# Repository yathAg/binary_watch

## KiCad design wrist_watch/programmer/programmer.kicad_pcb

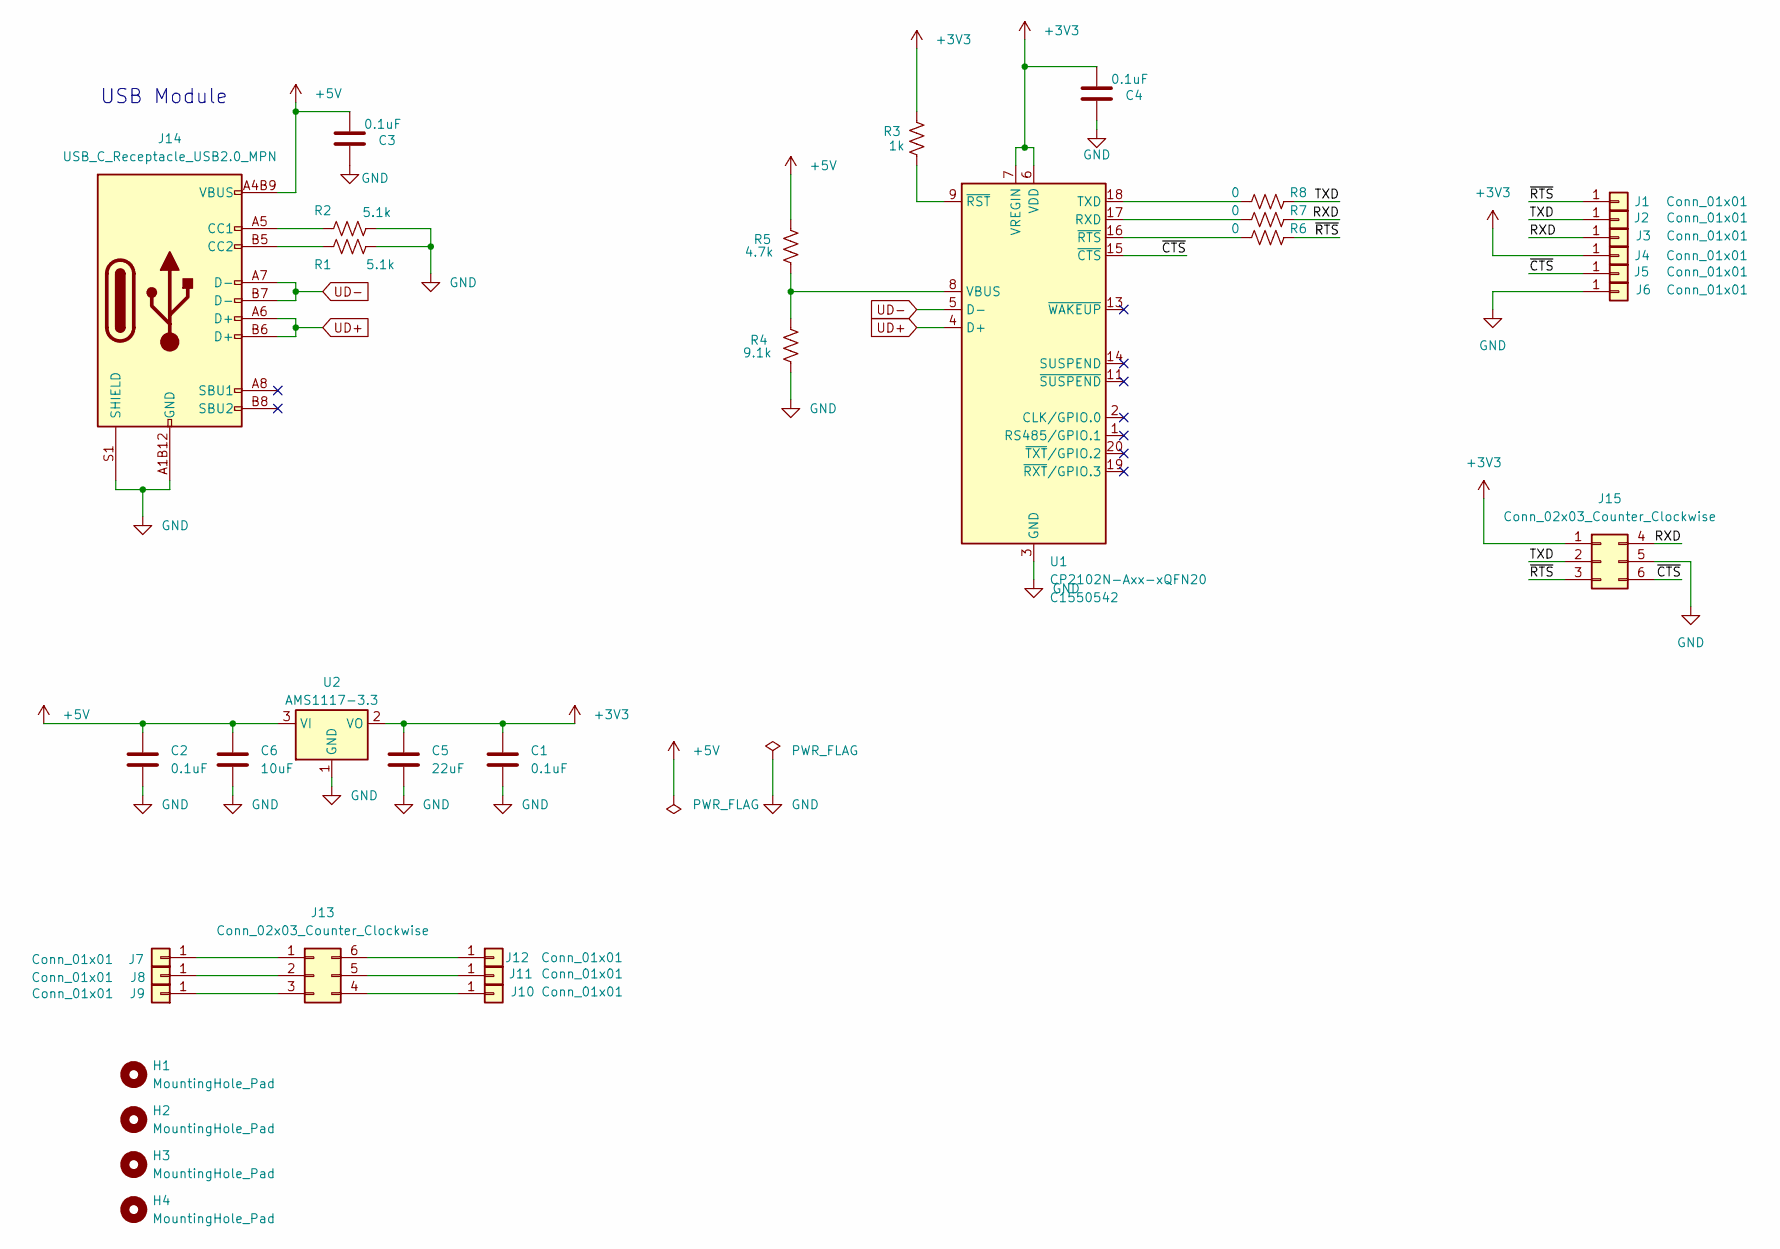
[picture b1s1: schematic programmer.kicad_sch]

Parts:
C1, C2, C3, C4: 0.1uF; C_0805_2012Metric; LCSC C1525
C5: 22uF; C_0805_2012Metric; LCSC C59461
C6: 10uF; C_0805_2012Metric; LCSC C19702
H1, H2, H3, H4: MountingHole_Pad; MountingHole_3.2mm_M3
J1, J2, J3, J4, J5, J6, J7, J8, J9, J10, J11, J12: Conn_01x01; TestPoint_Pad_D2.0mm
J13, J15: Conn_02x03_Counter_Clockwise; PinHeader_2x03_P2.54mm_Vertical
J14: USB_C_Receptacle_USB2.0_MPN; USB-C-YTC-TC16S-23; LCSC C393939
R1, R2: 5.1k; R_0805_2012Metric; LCSC C25905
R3: 1k; R_0805_2012Metric; LCSC C11702
R4: 9.1k; R_0805_2012Metric
R5: 4.7k; R_0805_2012Metric; LCSC C105871
R6, R7, R8: 0; R_0805_2012Metric
U1: CP2102N-Axx-xQFN20; SiliconLabs_QFN-20-1EP_3x3mm_P0.5mm_EP1.8x1.8mm; LCSC C1550542
U2: AMS1117-3.3; SOT-223-3_TabPin2; LCSC C94058

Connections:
+3V3: C1.1, C4.1, C5.1, J4.1, J15.1, R3.1, U1.6 (VDD), U1.7 (VREGIN), U2.2 (VO)
+5V: C2.1, C3.1, C6.1, J14.A4B9 (VBUS), J14.A9B4 (VBUS), R5.1, U2.3 (VI)
/RXD: J3.1, J15.4, R7.2
/TXD: J2.1, J15.2, R8.2
/~CTS: J5.1, J15.6, U1.15 (~CTS)
/~RTS: J1.1, J15.3, R6.2
GND: C1.2, C2.2, C3.2, C4.2, C5.2, C6.2, J6.1, J14.A1B12 (GND), J14.A12B1 (GND), J14.S1 (SHIELD), J15.5, R1.1, R2.1, R4.2, U1.3 (GND), U1.12 (GND), U1.21 (GND), U2.1 (GND)
unnamed: J10.1, J13.4
unnamed: J11.1, J13.5
unnamed: J12.1, J13.6
unnamed: J7.1, J13.1
unnamed: J8.1, J13.2
unnamed: J9.1, J13.3
unnamed: J14.A5 (CC1), R2.2
unnamed: J14.B5 (CC2), R1.2
unnamed: R7.1, U1.17 (RXD)
unnamed: R8.1, U1.18 (TXD)
unnamed: R4.1, R5.2, U1.8 (VBUS)
unnamed: R3.2, U1.9 (~RST)
unnamed: R6.1, U1.16 (~RTS)
UD+: J14.A6 (D+), J14.B6 (D+), U1.4 (D+)
UD-: J14.A7 (D-), J14.B7 (D-), U1.5 (D-)

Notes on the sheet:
USB Module

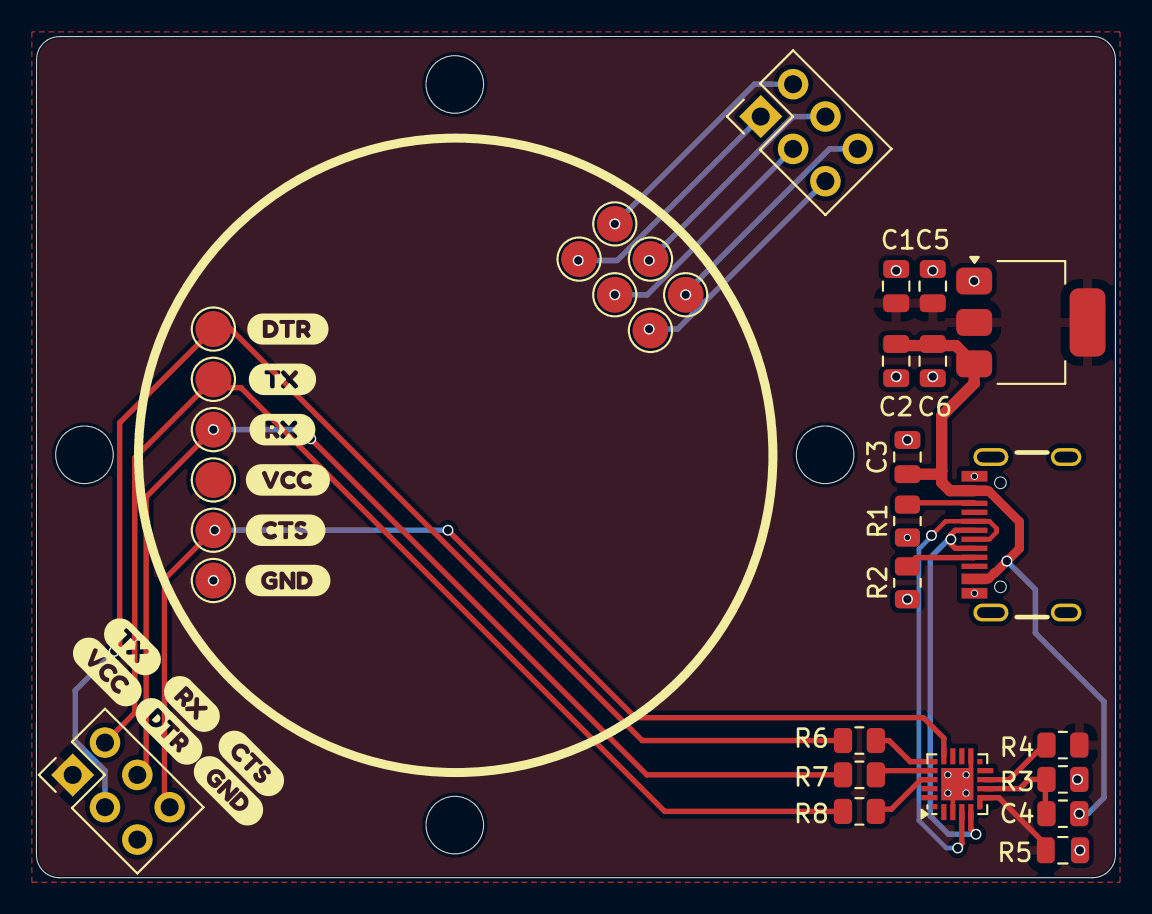
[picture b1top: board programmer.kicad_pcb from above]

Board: 2 copper layers, 59.9 x 46.7 mm, 47 parts (0 on the bottom side), 22 nets.

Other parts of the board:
kibuzzard-67CE1A96, kibuzzard-67CE1A96#2: G***; kibuzzard-67CE1A96
kibuzzard-67CE23F8, kibuzzard-67CE23F8#2: G***; kibuzzard-67CE23F8
kibuzzard-67CE240C, kibuzzard-67CE240C#2: G***; kibuzzard-67CE240C
kibuzzard-67CE241A, kibuzzard-67CE241A#2: G***; kibuzzard-67CE241A
kibuzzard-67CE249C, kibuzzard-67CE249C#2: G***; kibuzzard-67CE249C
kibuzzard-67CE2403, kibuzzard-67CE2403#2: G***; kibuzzard-67CE2403

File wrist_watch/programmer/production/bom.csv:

Designator,Footprint,Quantity,Value,LCSC Part #
"C1, C2, C3, C4",0805,4,0.1uF,C1525
C5,0805,1,22uF,C59461
C6,0805,1,10uF,C19702
"J1, J10, J11, J12, J2, J3, J4, J5, J6, J7, J8, J9",TestPoint_Pad_D2.0mm,12,Conn_01x01,
"J13, J15",PinHeader_2x03_P2.54mm_Vertical,2,Conn_02x03_Counter_Clockwise,
J14,USB-C-YTC-TC16S-23,1,USB_C_Receptacle_USB2.0_MPN,C393939
"R1, R2",0805,2,5.1k,C25905
R3,0805,1,1k,C11702
R4,0805,1,9.1k,
R5,0805,1,4.7k,C105871
"R6, R7, R8",0805,3,0,
U1,SiliconLabs_QFN-20-1EP_3x3mm_P0.5mm_EP1.8x1.8mm,1,CP2102N-Axx-xQFN20,C1550542
U2,SOT-223-3_TabPin2,1,AMS1117-3.3,C94058

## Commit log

2023-03-29 Renamed and cleaned code
2023-04-11 Added Libraries
2023-04-11 Working Code
2025-03-10 Programmer
2025-03-10 silkscreen update
2025-03-22 dir reorg
2025-03-22 New code ( not tested)
